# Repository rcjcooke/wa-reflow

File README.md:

# wa-reflow
Workshop Automation - Reflow Oven

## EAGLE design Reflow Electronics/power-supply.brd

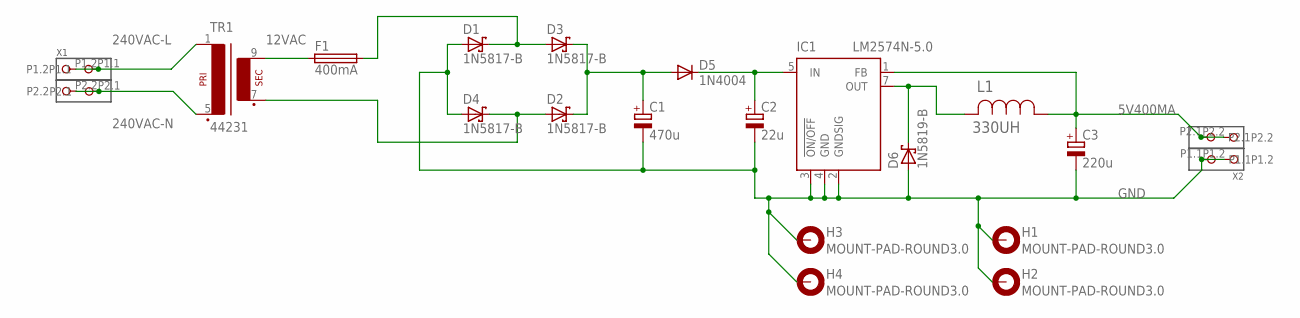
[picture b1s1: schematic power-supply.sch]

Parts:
C1: 470u; E3,5-8
C2: 22u; E2-4
C3: 220u; E2-5
D1, D2, D3, D4: 1N5817-B; DO41-7.6
D5: 1N4004; DO41-10
D6: 1N5819-B; DO41-7.6
F1: 400mA; SH22,5
H1, H2, H3, H4: MOUNT-PAD-ROUND3.0; 3,0-PAD
IC1: LM2574N-5.0; DIL08
L1: 330UH; IND_ELC11D
TR1: 44231; EI42-1
X1, X2: 2604-1102; P-2604-1102

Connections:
5V400MA: C3.+, IC1.1 (FB), L1.1, X2.P2.1, X2.P2.2
12VAC: F1.1, TR1.9 (S4)
240VAC-L: TR1.1, X1.P1.1, X1.P1.2
240VAC-N: TR1.5 (P2), X1.P2.1, X1.P2.2
GND: C1.-, C2.-, C3.-, D1.A, D4.A, D6.A, H1.B3,0, H2.B3,0, H3.B3,0, H4.B3,0, IC1.2 (GNDSIG), IC1.3 (!ON/OFF), IC1.4 (GND), X2.P1.1, X2.P1.2
unnamed: C2.+, D5.C, IC1.5 (IN)
unnamed: C1.+, D2.C, D3.C, D5.A
unnamed: D1.C, D3.A, F1.2
unnamed: D2.A, D4.C, TR1.7 (S3)
unnamed: D6.C, IC1.7 (OUT), L1.2

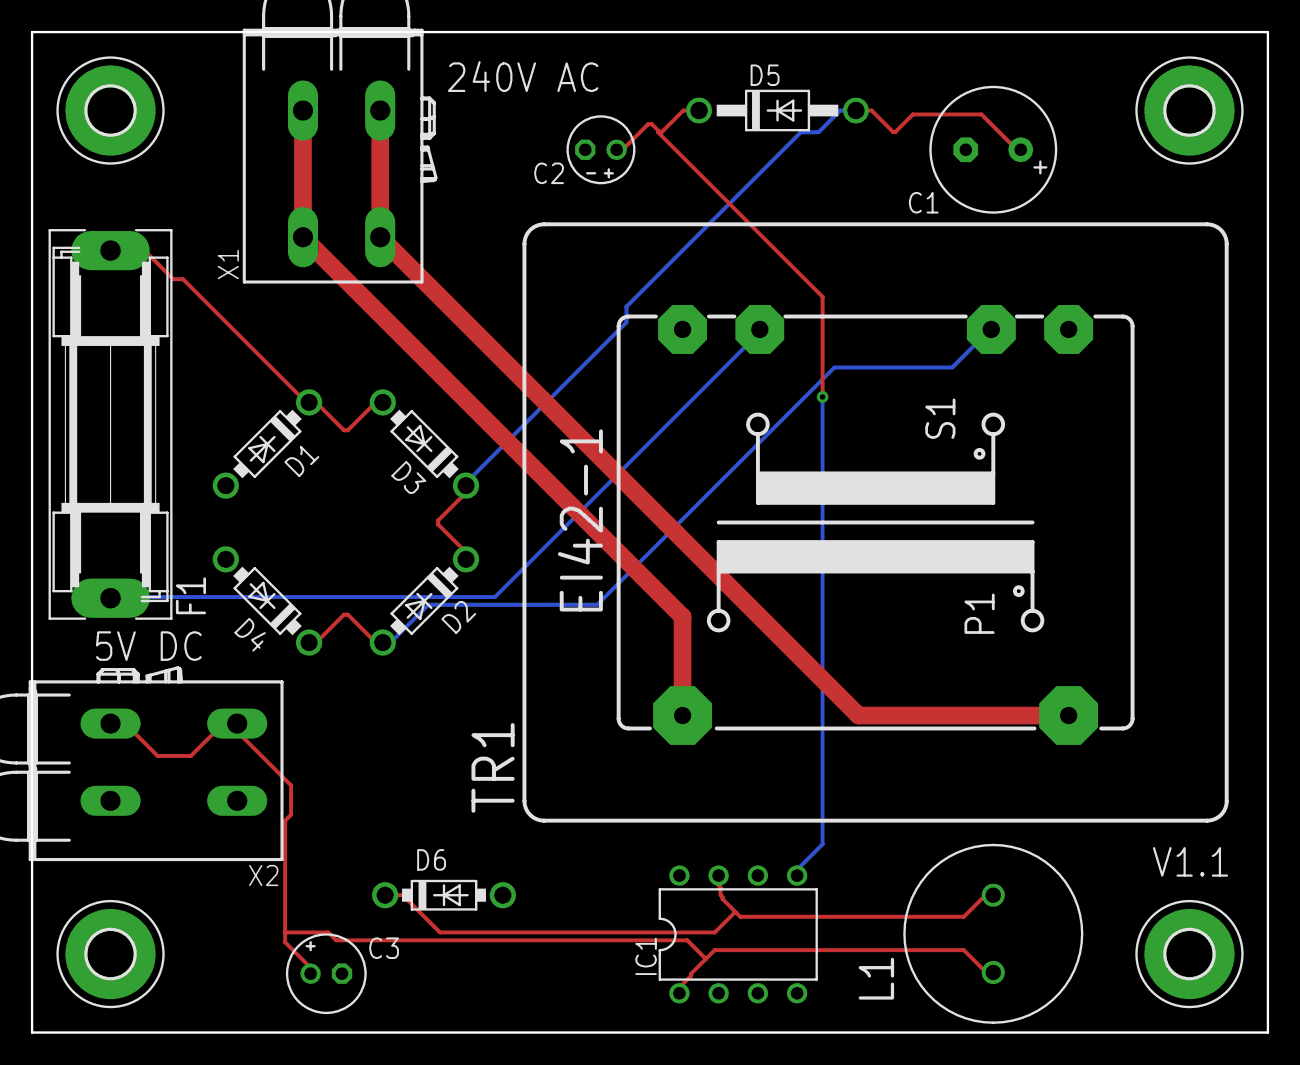
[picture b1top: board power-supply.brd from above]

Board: 2 copper layers, 80.0 x 64.8 mm, 19 parts (0 on the bottom side), 10 nets.

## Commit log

2018-06-10 Power Supply schematics, board and Gerbers for build with OSHPark
2018-06-10 Datasheets for devices used
2018-06-22 power supply electronics
2018-07-11 Fixed schematic and board for problems found on first iteration
2018-07-12 Tweaked power supply for future following testing. Added BOM.
2018-07-19 Moved some folders around and renamed them to align with my new standard
2018-07-19 Added first cut of code from basics-multiplespislaves.
2018-07-19 First cut of functional code
2018-07-19 Working onfirst screen
2018-07-19 Added abort button. Added state.
2018-07-19 pulled out text colour
2018-07-20 Added first basic profile
2018-07-20 Got basic reflow profile graph plot working
2018-07-20 Added oven state to basic overall model and tied to screen
2018-07-22 hooking tmperature up to model
2018-07-22 Added refreshable interface
2018-07-22 Fixed some bugs
2018-07-22 Refactor to pull apart user screens
2018-07-23 Sorting out selection screen
2018-07-23 Got list rendering working
2018-07-23 Dealing with user interaction
2018-07-23 Tied in switch refresh
2018-07-25 Change folder name to better conform to Arduino standards.
2018-07-26 Getting selector switch hooked up. Starting Heater.
2018-07-26 Sorted out target temperature at time
2018-07-26 Sorted out heater relay mechanics
2018-07-26 Added pull down to switch input pin
2018-07-26 Time remaining updates
2018-07-26 Fixed pre-c2017 confusion re static constexpr char[] declaration vs definition
2018-07-26 Added reflow progress graph plotting
2018-07-26 Added Reflow Zone name display update
2018-08-11 Tying everything together
2018-08-11 Finally sorted out the profile memory issue
2018-08-12 Sorting out target temperature
2018-08-12 Added loads of debug
2018-08-12 Sorting out state update
2018-08-12 Fixed runtime temp plotting
2018-08-18 Fixed switch definition typo
2018-08-18 Added some button debouncing
2018-08-24 Added esp-wrover-kit target for debugging
